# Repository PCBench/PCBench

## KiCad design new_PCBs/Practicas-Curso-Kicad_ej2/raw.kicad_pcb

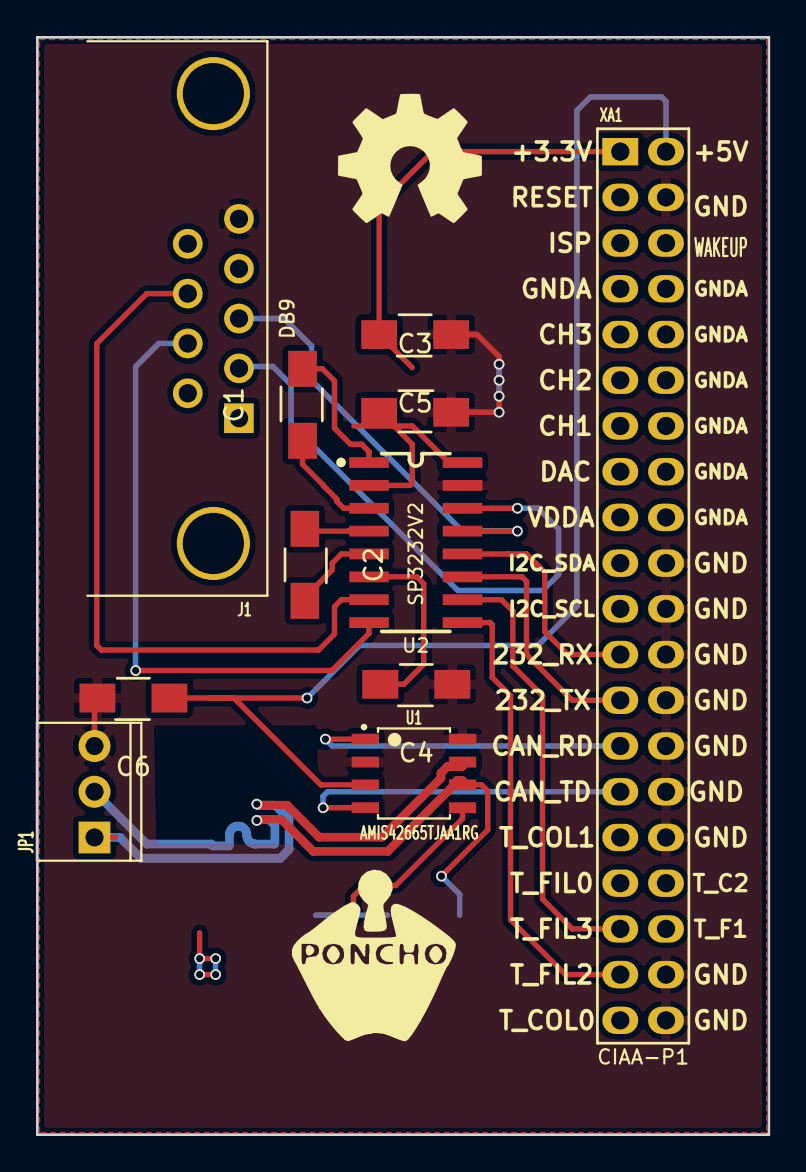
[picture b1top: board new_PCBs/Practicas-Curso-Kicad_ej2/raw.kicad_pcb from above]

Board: 2 copper layers, 40.6 x 61.0 mm, 14 parts (0 on the bottom side), 22 nets.

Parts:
C1, C2, C3, C4, C5: C; C_1206_HandSoldering
C6: 100uF; C_1206_HandSoldering
G101: Logo_OSHWA
J1: DB9; DB9_F_TH
JP1: CONN_3; CON_PALETA_3
R1, R2: 60; R_1206_HandSoldering
U1: AMIS42665TJAA1RG; SOIC-8
U2: SP3232V2; SP3232ECN-SOIC16N
XA1: Conn_Poncho2P_2x_20x2; Conn_Poncho_Derecha

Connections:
+3.3V: C5.1, U2.16, XA1.1
+5V: C6.2, U1.3, XA1.2
/conector y can/CAN_N: JP1.2, R2.2, U1.6
/conector y can/CAN_P: JP1.1, R1.1, U1.7
/conector y can/CAN_RX: U1.4, XA1.29
/conector y can/CAN_TX: U1.1, XA1.27
/conector y can/CTS: U2.10, XA1.35
/conector y can/RTS: U2.9, XA1.37
/conector y can/RXD: U2.11, XA1.25
/conector y can/TXD: U2.12, XA1.23
GND: C3.1, C4.2, C5.2, C6.1, J1.5, JP1.3, U1.2, U1.8, U2.15, XA1.4, XA1.20, XA1.22, XA1.24, XA1.26, XA1.28, XA1.30, XA1.32, XA1.38, XA1.40
unnamed: C1.1, U2.1
unnamed: C1.2, U2.3
unnamed: C2.1, U2.5
unnamed: C2.2, U2.4
unnamed: C3.2, U2.2
unnamed: C4.1, U2.6
unnamed: J1.2, U2.14
unnamed: J1.3, U2.13
unnamed: J1.7, U2.8
unnamed: J1.8, U2.7
unnamed: R1.2, R2.1, U1.5

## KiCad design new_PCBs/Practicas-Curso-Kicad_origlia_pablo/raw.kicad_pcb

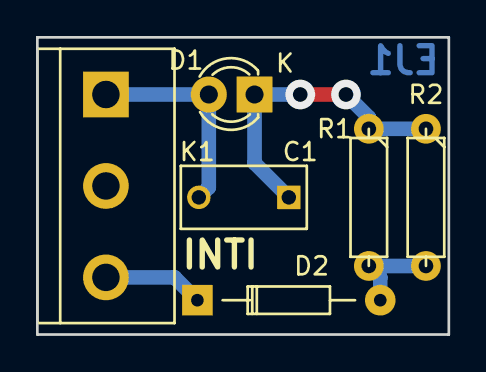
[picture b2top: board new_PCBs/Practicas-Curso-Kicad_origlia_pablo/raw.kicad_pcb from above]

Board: 2 copper layers, 22.9 x 16.5 mm, 6 parts (0 on the bottom side), 4 nets.

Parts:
C1: 100 nF; C_Rect_L7_W3.5_P5
D1: LED ROJO; LED-3MM
D2: 1N4148; Diode_DO-35_SOD27_Horizontal_RM10
K1: CONN_3; bornier3
R1, R2: 100K; R3-LARGE_PADS

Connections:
unnamed: C1.1, D1.1, R1.1, R2.1
unnamed: C1.2, D1.2, K1.1
unnamed: D2.1, K1.3
unnamed: D2.2, R1.2, R2.2

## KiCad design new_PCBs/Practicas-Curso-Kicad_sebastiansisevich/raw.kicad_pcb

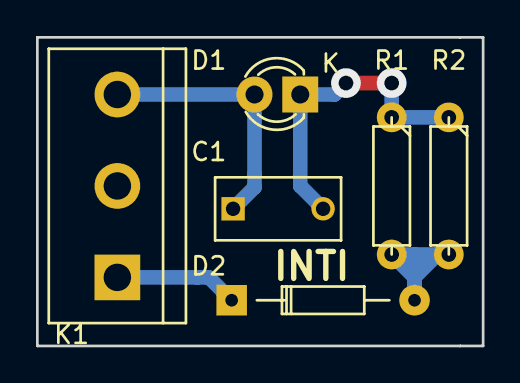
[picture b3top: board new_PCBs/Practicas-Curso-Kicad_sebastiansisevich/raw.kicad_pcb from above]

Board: 2 copper layers, 24.8 x 17.1 mm, 6 parts (0 on the bottom side), 4 nets.

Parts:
C1: 100nf; C_Rect_L7_W3.5_P5
D1: LED ROJO; LED-3MM
D2: 1N4148; Diode_DO-35_SOD27_Horizontal_RM10
K1: CONN_3; bornier3
R1, R2: 100K; R3-LARGE_PADS

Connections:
unnamed: C1.1, D1.2, K1.3
unnamed: C1.2, D1.1, R1.1, R2.1
unnamed: D2.1, K1.1
unnamed: D2.2, R1.2, R2.2

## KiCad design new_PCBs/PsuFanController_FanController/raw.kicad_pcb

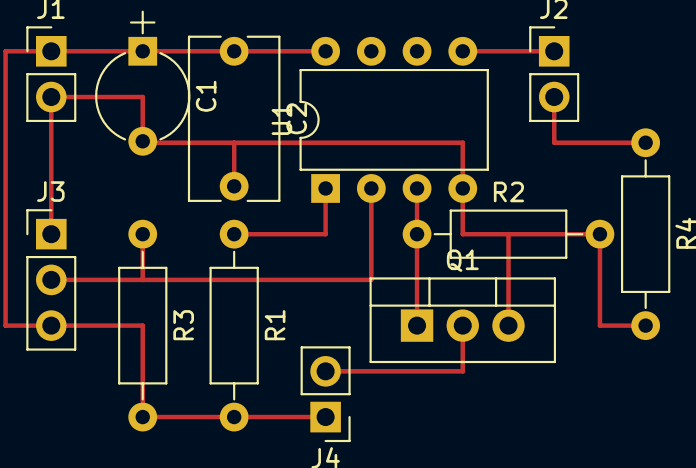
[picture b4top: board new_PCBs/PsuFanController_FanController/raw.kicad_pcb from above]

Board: 2 copper layers, 12 parts (0 on the bottom side), 8 nets.

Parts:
C1: 1uF; CP_Radial_Tantal_D5.0mm_P5.00mm
C2: 0.1uF; C_Rect_L9.0mm_W4.9mm_P7.50mm_MKT
J1: PWR; Pin_Header_Straight_1x02_Pitch2.54mm
J2: LED; Pin_Header_Straight_1x02_Pitch2.54mm
J3: DS18B20; Pin_Header_Straight_1x03_Pitch2.54mm
J4: Fan; Pin_Header_Straight_1x02_Pitch2.54mm
Q1: IRL3103PBF; TO-220_Vertical
R1, R2: 10K; R_Axial_DIN0207_L6.3mm_D2.5mm_P10.16mm_Horizontal
R3: 4K7; R_Axial_DIN0207_L6.3mm_D2.5mm_P10.16mm_Horizontal
R4: 270; R_Axial_DIN0207_L6.3mm_D2.5mm_P10.16mm_Horizontal
U1: ATTINY85-20PU; DIP-8_W7.62mm

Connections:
/VCC: C1.1, C2.1, J1.1, J3.3, J4.1, R1.2, R3.2, U1.8
GND: C1.2, C2.2, J1.2, J3.1, Q1.3, R2.2, R4.2, U1.4
unnamed: J2.1, U1.5
unnamed: J2.2, R4.1
unnamed: J3.2, R3.1, U1.2
unnamed: J4.2, Q1.2
unnamed: Q1.1, R2.1, U1.3
unnamed: R1.1, U1.1

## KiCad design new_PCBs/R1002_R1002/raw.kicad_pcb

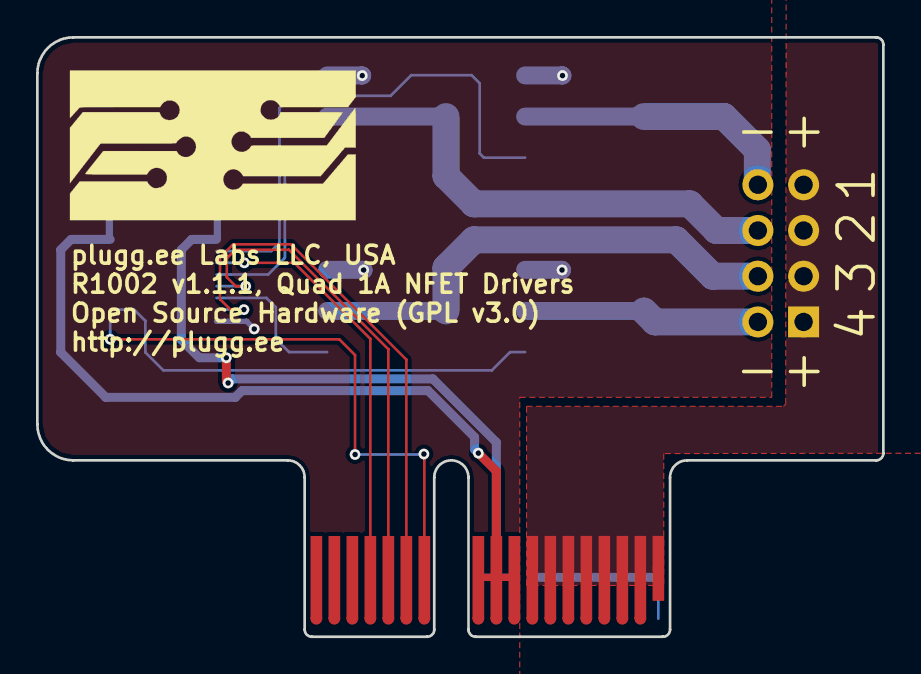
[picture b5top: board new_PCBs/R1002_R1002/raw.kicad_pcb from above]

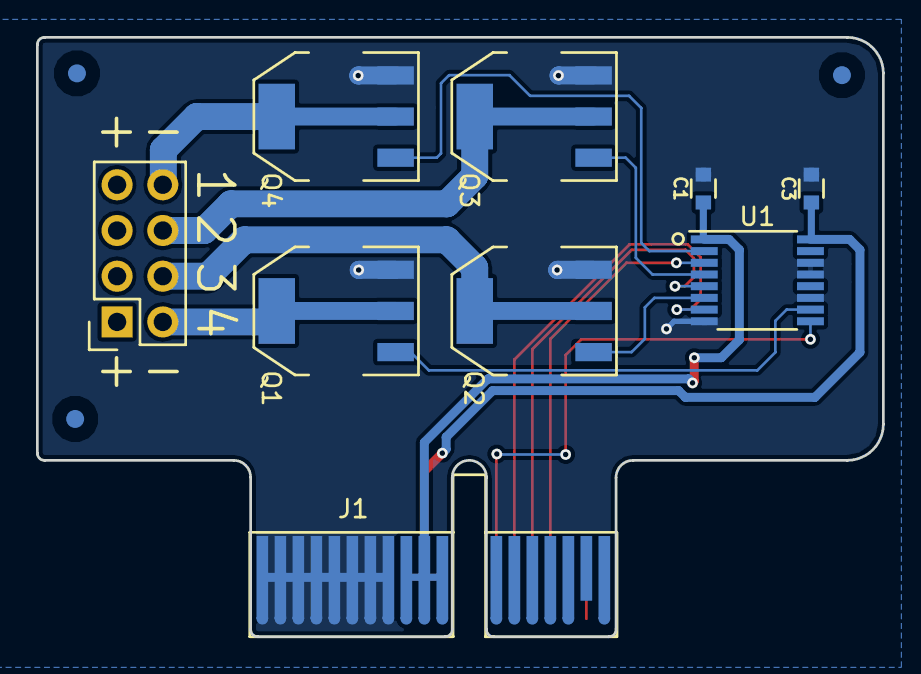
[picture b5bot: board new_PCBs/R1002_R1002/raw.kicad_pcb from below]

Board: 2 copper layers, 47.0 x 33.3 mm, 13 parts (12 on the bottom side), 16 nets.

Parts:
A1: ART; pluggeeLabsIcon-16X8
C1, C3: CC0603KRX7R9BB104; CAPC0603
FID1, FID2, FID3: FIDTOP001
J1: PCIEXPRESS-X1
J2: CONN254P-02X04
Q1, Q2, Q3, Q4: Q_NMOS_GDSD; SOT-223
U1: MC14504B-TSSOP; SOP65P500X440X120-16

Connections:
+3V3: C1.1, J1.B9, J1.B10, J1.B11, U1.1
+5V: C3.1, J1.A9, J1.A10, J1.A11, U1.16
/DN1: J2.8, Q4.2, Q4.4
/DN2: J2.6, Q3.2, Q3.4
/DN3: J2.4, Q2.2, Q2.4
/DN4: J2.2, Q1.2, Q1.4
/GN1: Q4.1, U1.2
/GN2: Q3.1, U1.4
/GN3: Q2.1, U1.6
/GN4: Q1.1, U1.10
GND: C1.2, C3.2, J1.B1, J1.B2, J1.B3, J1.B4, J1.B5, J1.B6, J1.B7, J1.B8, Q1.3, Q2.3, Q3.3, Q4.3, U1.8, U1.11, U1.13, U1.14
HT: J1.A1, J1.A2, J1.A3, J1.A4, J1.A5, J1.A6, J1.A7, J1.A8, J2.1, J2.3, J2.5, J2.7
PX1: J1.A12, U1.9
PX2: J1.A13, U1.7
PX3: J1.A14, U1.5
PX4: J1.A15, U1.3

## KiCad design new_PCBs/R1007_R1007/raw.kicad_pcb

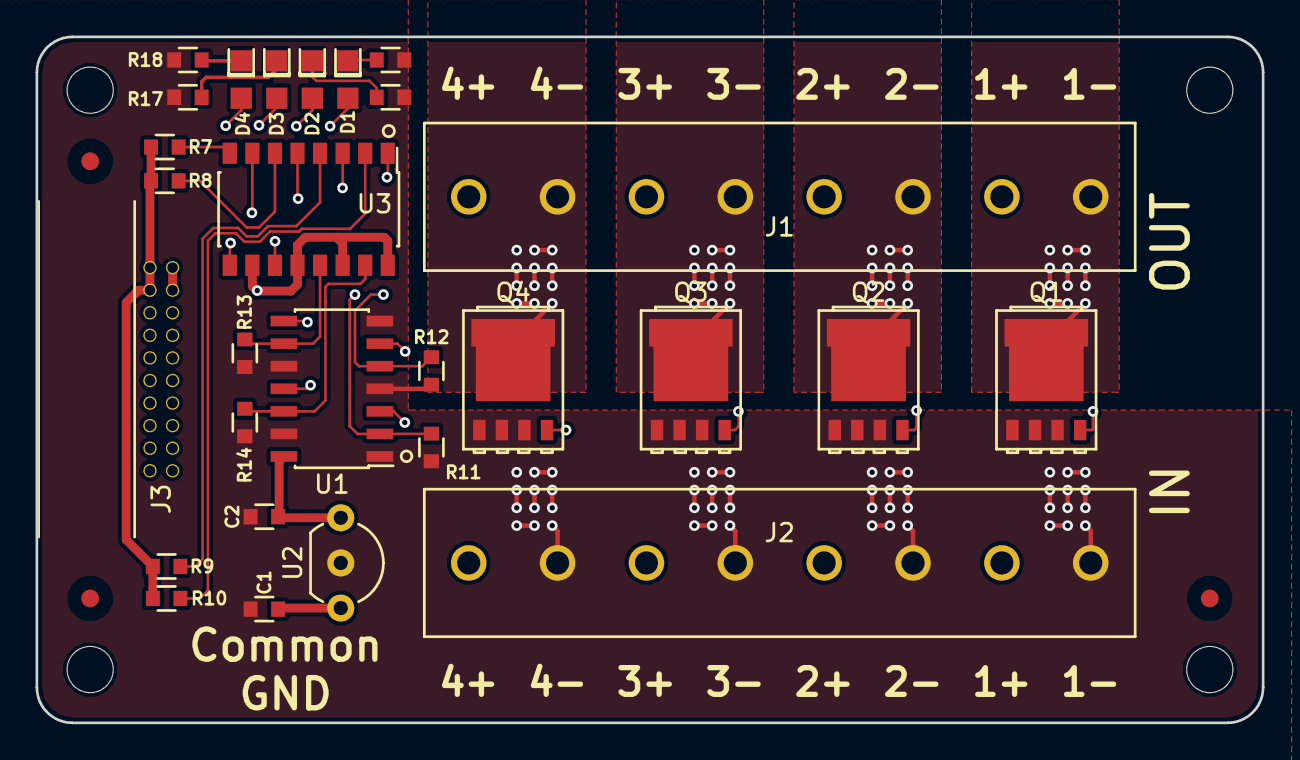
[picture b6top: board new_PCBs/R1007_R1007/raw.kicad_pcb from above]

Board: 4 copper layers, 69.0 x 38.6 mm, 36 parts (1 on the bottom side), 32 nets.

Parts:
A1: ART; pluggeeLabsIcon-13X7
C1, C2: CC0603KRX7R9BB104; CAPC0603
D1, D2, D3, D4: LTW-170TK; DIOC200X120X110
FID1, FID2, FID3: FIDTOP001
J1, J2: CONN500P-01X08
J3: CONN_R1000A_EXTENSION; CONN127P-02X10
MP1, MP2, MP3, MP4: MECH_NPTH_M3
Q1, Q2, Q3, Q4: PSMN1R2-30YLC; SOT127P500X110-5
R7, R8, R9, R10, R15, R16, R17, R18: RC0603FR-071KL; RESC0603
R11, R12, R13, R14: RC0603FR-074K7L; RESC0603
U1: 74HC125; SOIC127P870X390X175-14
U2: AS78L05ZTR-E1; TO92_AMMO
U3: TLP293-4; SOIC127P1030X455X210-16

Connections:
+5P: C2.1, U1.14, U2.1, U3.10, U3.12, U3.14, U3.16
/GN1: D1.2, Q1.4, U1.11
/GN2: D2.2, Q2.4, U1.8
/GN3: D3.2, Q3.4, U1.6
/GN4: D4.2, Q4.4, U1.3
/IGN1: R14.1, U1.12, U3.15
/IGN2: R13.1, U1.9, U3.13
/IGN3: R12.1, U1.5, U3.11
/IGN4: R11.1, U1.2, U3.9
/INR1: R10.1, U3.2
/INR2: R9.1, U3.4
/INR3: R8.1, U3.6
/INR4: R7.1, U3.8
/N1: J1.1, Q1.5
/N2: J1.3, Q2.5
/N3: J1.5, Q3.5
/N4: J1.7, Q4.5
/VDD2: J1.6, J2.3
/VDD3: J1.4, J2.5
/VDD4: J1.2, J2.7
GND: J3.18, J3.20, R7.2, R8.2, R9.2, R10.2
GNDPWR: C1.2, C2.2, J2.2, J2.4, J2.6, J2.8, Q1.1, Q1.2, Q1.3, Q2.1, Q2.2, Q2.3, Q3.1, Q3.2, Q3.3, Q4.1, Q4.2, Q4.3, R11.2, R12.2, R13.2, R14.2, R15.2, R16.2, R17.2, R18.2, U1.1, U1.4, U1.7, U1.10, U1.13, U2.2
HT: J3.17, J3.19
unnamed: D1.1, R15.1
unnamed: D2.1, R16.1
unnamed: D3.1, R17.1
unnamed: D4.1, R18.1
PX1: J3.13, U3.1
PX2: J3.11, U3.3
PX3: J3.9, U3.5
PX4: J3.7, U3.7
VDD: C1.1, J1.8, J2.1, U2.3

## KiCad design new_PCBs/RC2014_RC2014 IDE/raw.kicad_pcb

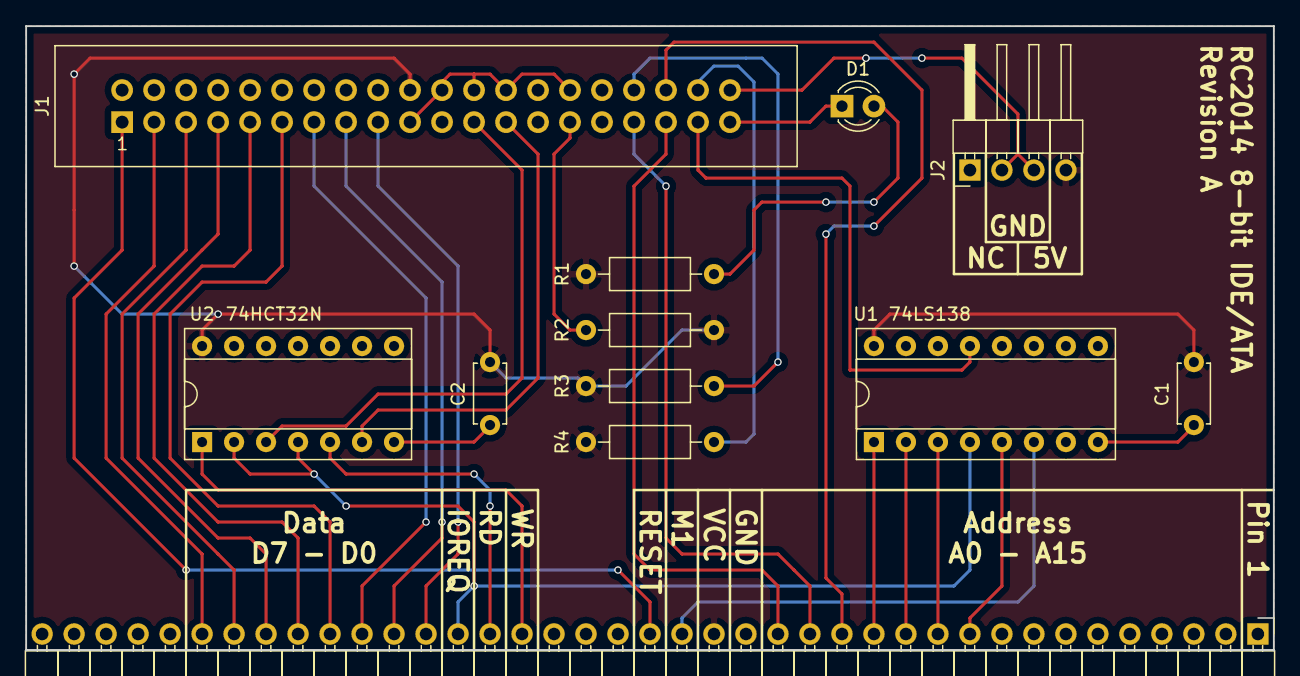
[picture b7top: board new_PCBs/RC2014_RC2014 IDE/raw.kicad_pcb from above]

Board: 2 copper layers, 99.1 x 49.5 mm, 12 parts (0 on the bottom side), 30 nets.

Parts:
C1, C2: 100nF; C_Disc_D4.7mm_W2.5mm_P5.00mm
D1: LED; LED_D3.0mm
J1: CONN_02X20; IDC_Header_Straight_40pins
J2: Device power; Pin_Header_Angled_1x04_Pitch2.54mm
J4: CONN_01X39; Pin_Header_Angled_1x39_Pitch2.54mm
R1: 330; R_Axial_DIN0207_L6.3mm_D2.5mm_P10.16mm_Horizontal
R2, R3, R4: 1k; R_Axial_DIN0207_L6.3mm_D2.5mm_P10.16mm_Horizontal
U1: 74LS138; DIP-16_W7.62mm_Socket
U2: 74HCT32N; DIP-14_W7.62mm_Socket

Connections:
/IORD: J1.25, U2.6
/IOWR: J1.23, U2.3
A0: J1.35, J4.16
A1: J1.33, J4.15
A2: J1.36, J4.14
A3: J4.13, U1.1
A4: J4.12, U1.2
A5: J4.11, U1.3
A6: J4.10, U1.5
BUSY: D1.1, J1.39
D0: J1.17, J4.27
D1: J1.15, J4.28
D2: J1.13, J4.29
D3: J1.11, J4.30
D4: J1.9, J4.31
D5: J1.7, J4.32
D6: J1.5, J4.33
D7: J1.3, J4.34
GND: C1.2, C2.2, J1.2, J1.19, J1.22, J1.24, J1.26, J1.30, J1.40, J2.2, J2.3, J4.17, U1.8, U2.7, U2.9, U2.10, U2.12, U2.13
IOREQ: J4.26, U1.4, U2.2, U2.4
M1: J4.19, U1.6
unnamed: D1.2, R1.1
unnamed: J1.29, R2.1
unnamed: J1.34, R3.2
unnamed: J1.38, R4.2
PORT16: J1.37, U1.13
RD: J4.25, U2.5
RESET: J1.1, J4.20
VCC: C1.1, C2.1, J1.20, J2.4, J4.18, R1.2, R2.2, R3.1, R4.1, U1.16, U2.14
WR: J4.24, U2.1

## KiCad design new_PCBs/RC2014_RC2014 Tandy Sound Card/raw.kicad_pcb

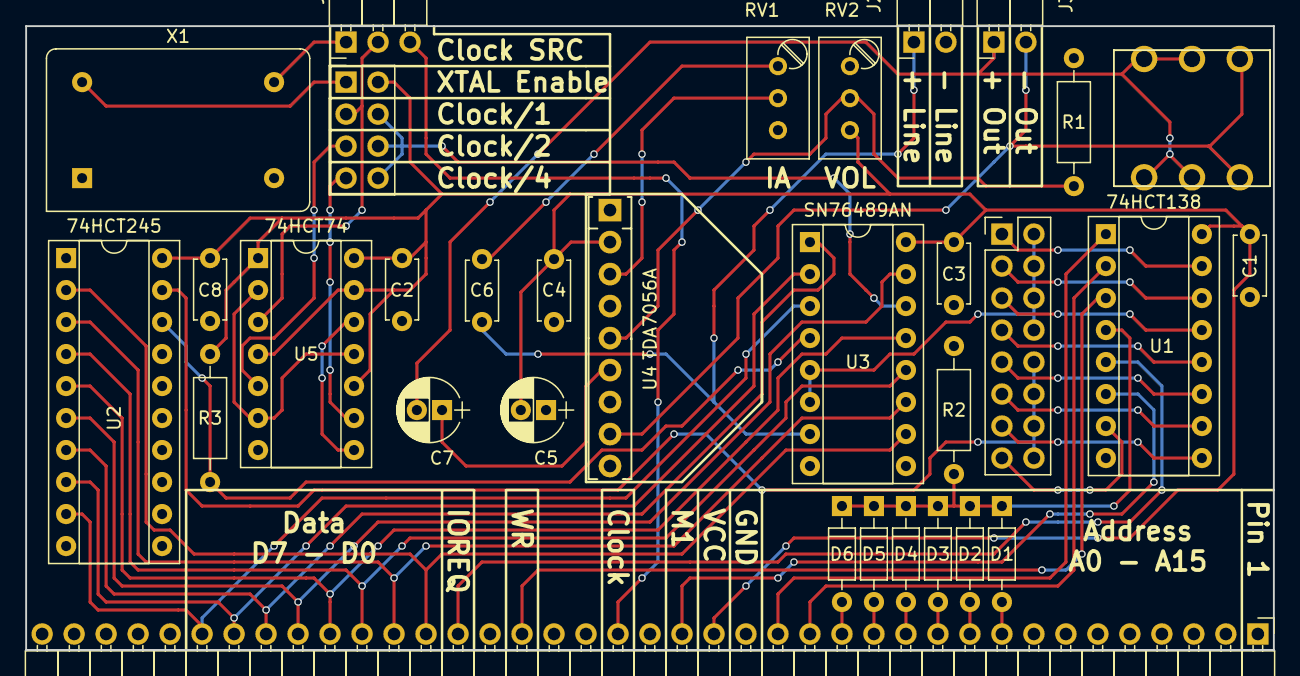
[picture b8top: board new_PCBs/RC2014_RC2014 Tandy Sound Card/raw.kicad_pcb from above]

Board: 2 copper layers, 99.1 x 49.5 mm, 32 parts (0 on the bottom side), 49 nets.

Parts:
C1, C2, C3, C4, C8: 100nF; C_Disc_D4.7mm_W2.5mm_P5.00mm
C5: 220uF; CP_Radial_D5.0mm_P2.00mm
C6: 470nF; C_Disc_D4.7mm_W2.5mm_P5.00mm
C7: 470uF; CP_Radial_D5.0mm_P2.00mm
D1, D2, D3, D4, D5, D6: 1N4848; D_DO-35_SOD27_P7.62mm_Horizontal
J1: CONN_01X39; Pin_Header_Angled_1x39_Pitch2.54mm
J2: Line Out; Pin_Header_Angled_1x02_Pitch2.54mm
J3: Speaker Out; Pin_Header_Angled_1x02_Pitch2.54mm
J4: CONN_02X08; Pin_Header_Straight_2x08_Pitch2.54mm
J5: JACK_TRS_6PINS; cliff_fcr1295_socket
J6: CONN_02X04; Pin_Header_Straight_2x04_Pitch2.54mm
JP1: Clock source; Pin_Header_Angled_1x03_Pitch2.54mm
R1: 1k; R_Axial_DIN0207_L6.3mm_D2.5mm_P10.16mm_Horizontal
R2, R3: 10k; R_Axial_DIN0207_L6.3mm_D2.5mm_P10.16mm_Horizontal
RV1, RV2: 10k; Potentiometer_Trimmer_Bourns_3296W
U1: 74HCT138; DIP-16_W7.62mm_Socket
U2: 74HCT245; DIP-20_W7.62mm_Socket
U3: SN76489AN; DIP-16_W7.62mm_Socket
U4: TDA7056A; SIP9_Housing
U5: 74HCT74; DIP-14_W7.62mm_Socket
X1: 1MHz; Oscillator_DIP-14

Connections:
/RD_Port_0: J4.9, U1.11
/RD_Port_1: J4.11, U1.10
/RD_Port_2: J4.13, U1.9
/RD_Port_3: J4.15, U1.7
/WR_Port_0: J4.1, U1.15
/WR_Port_1: J4.3, U1.14
/WR_Port_2: J4.5, U1.13
/WR_Port_3: J4.7, U1.12
A0: J1.16, U1.1
A1: J1.15, U1.2
A2: D6.2, J1.14
A3: D5.2, J1.13
A4: D4.2, J1.12
A5: D3.2, J1.11
A6: D2.2, J1.10
A7: D1.2, J1.9
CLOCK: J1.21, JP1.3
CLOCK/1: J6.3, JP1.2, U5.3
CLOCK/2: J6.5, U5.5
CLOCK/4: J6.7, U5.9
D0: J1.27, U2.2, U3.10
D1: J1.28, U2.3, U3.11
D2: J1.29, U2.4, U3.12
D3: J1.30, U2.5, U3.13
D4: J1.31, U2.6, U3.15
D5: J1.32, U2.7, U3.1
D6: J1.33, U2.8, U3.2
D7: J1.34, U2.9, U3.3
GND: C1.2, C2.2, C3.2, C4.1, C5.1, C8.2, J1.17, J2.2, R1.2, R2.2, RV1.3, RV2.1, U1.8, U2.1, U2.10, U2.11, U2.12, U2.13, U2.14, U2.15, U2.16, U2.17, U3.8, U4.4, U4.7, U5.7, X1.7
IOREQ: J1.26, U1.5
IO_RD: J4.10, J4.12, J4.14, J4.16, U2.19
IO_WR: J4.2, J4.4, J4.6, J4.8, U3.5, U3.6
M1: J1.19, U1.6
unnamed: C6.2, RV1.1
unnamed: C7.2, J3.1, J5.2, J5.3, J5.5, J5.6
unnamed: D1.1, D2.1, D3.1, D4.1, D5.1, D6.1, R2.1, U1.4
unnamed: J6.1, X1.14
unnamed: JP1.1, X1.8
unnamed: R1.1, RV2.2, U4.5
unnamed: R3.2, U2.18, U3.4
unnamed: RV1.2, U4.3
unnamed: U5.2, U5.6, U5.11
unnamed: U5.8, U5.12
SND_CLOCK: J6.4, J6.6, J6.8, U3.14
SND_OUT: C6.1, J2.1, U3.7
SPKR_OUT+: C7.1, U4.6
SPKR_OUT-: J3.2, J5.1, J5.4, U4.8
VCC: C1.1, C2.1, C3.1, C4.2, C5.2, C8.1, J1.18, J6.2, R3.1, RV2.3, U1.16, U2.20, U3.16, U4.2, U5.1, U5.4, U5.10, U5.13, U5.14
WR: J1.24, U1.3

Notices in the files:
new_PCBs/R1002_R1002/raw.kicad_pcb:
Open Source Hardware (GPL v3.0)
